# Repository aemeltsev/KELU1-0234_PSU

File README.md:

# KELU1-0234PSU

![PCB image][KELU1-0234-PCB]

[KELU1-0234-PCB]: https://github.com/aemeltsev/KELU1-0234_PSU/blob/master/hw/KELU1-0234PSU_0.1rev.A/KELU1-0234-PCB.png

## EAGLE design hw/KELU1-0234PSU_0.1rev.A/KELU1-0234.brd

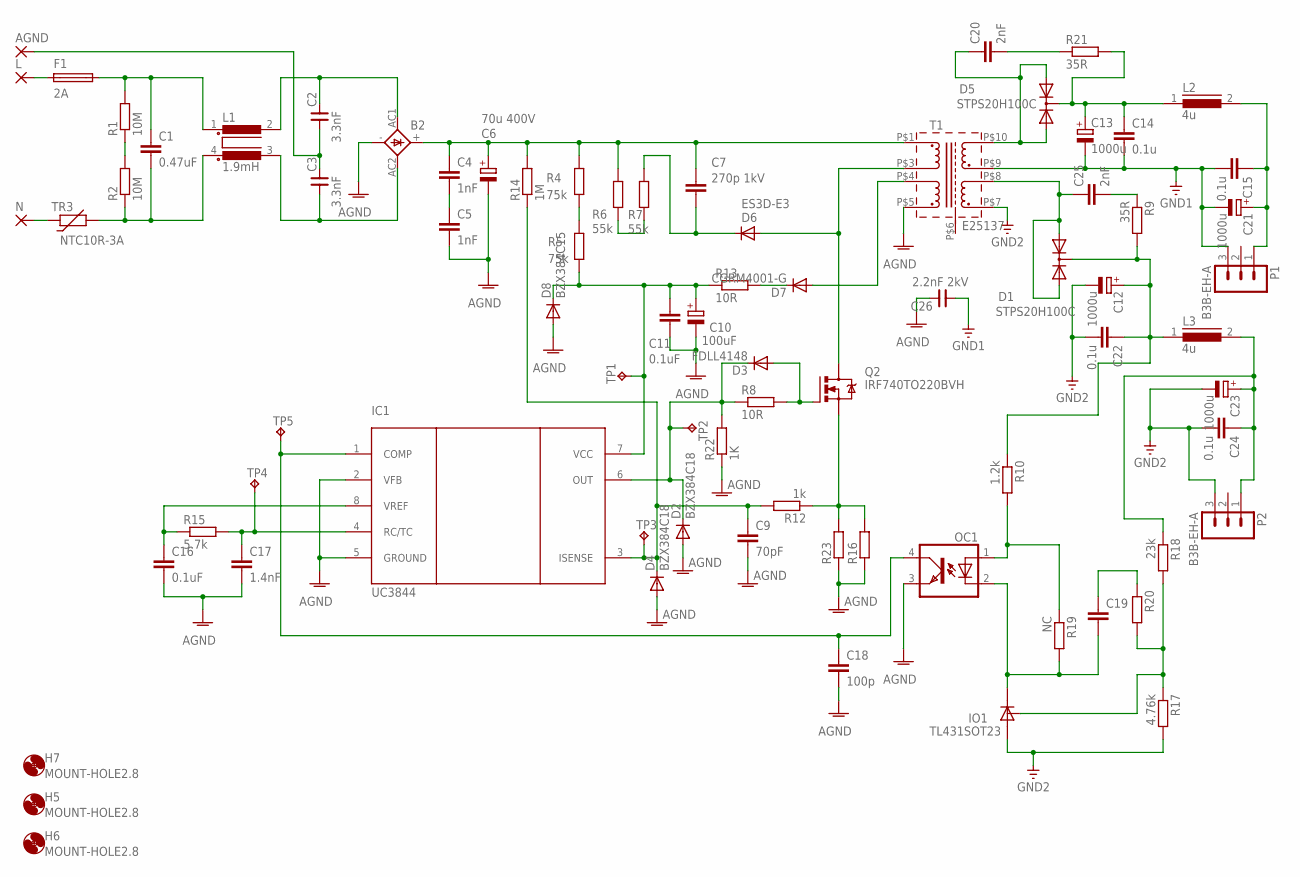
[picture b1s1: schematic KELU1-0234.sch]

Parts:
AGND: 3,17/1,1
B2: 2KBP
C1: 0.47uF; C15B5
C2: 3.3nF; C085-110X050
C3: 3.3nF; C080-110X045
C4, C5: 1nF; C1206K
C6: 70u 400V; E7,5-16
C7: 270p 1kV; C1206K
C9: 70pF; C0805K
C10: 100uF; E5-5
C11, C16: 0.1uF; C0805K
C12, C13, C21, C23: 1000u; E3,5-8
C14, C15, C22, C24: 0.1u; C0805K
C17: 1.4nF; C0805K
C18: 100p; C0805K
C19: C-EUC0805K; C0805K
C20, C25: 2nF; C1206K
C26: 2.2nF 2kV; C080-110X045
D1, D5: STPS20H100C; TO220ABS
D2, D4: BZX384C18; SOD323-W
D3: FDLL4148; MINIMELF
D6: ES3D-E3; SMC
D7: CGRM4001-G; SOD-123_MINI-SMA
D8: BZX384C15; SOD323-W
F1: 2A; TE5
H5, H6, H7: MOUNT-HOLE2.8; 2,8
IC1: UC3844; SOIC08
IO1: TL431SOT23; SOT23
L: 3,17/1,1
L1: 1.9mH; MFE
L2, L3: 4u; 82114R
N: 3,17/1,1
OC1: PC817; DIL04
P1, P2: B3B-EH-A
Q2: IRF740TO220BVH; TO220BVH
R1, R2: 10M; M1206
R4, R5: 75k; M1206
R6, R7: 55k; M1206
R8: 10R; M1206
R9, R21: 35R; M1206
R10: 1.2k; R0805W
R12: 1k; R0805W
R13: 10R; R0805W
R14: 1M; M1206
R15: 5.7k; R0805W
R16, R23: R-EU_R2512; R2512
R17: 4.76k; R0805W
R18: 23k; R0805W
R19: NC; R0805W
R20: R-EU_R0805W; R0805W
R22: 1K; M1206
T1: E25137
TP1, TP2, TP3, TP4, TP5: TPB1,27; B1,27
TR3: NTC10R-3A; R-5

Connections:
AGND: B2.-, C5.2, C6.-, C9.2, C10.-, C11.2, C16.2, C17.2, C18.2, C26.2, D2.A, D4.A, D8.A, IC1.2 (VFB), IC1.5 (GROUND), OC1.3 (EMIT), R16.1, R22.1, R23.1, T1.P$5 (5)
GND1: C13.-, C14.2, C15.2, C21.-, C26.1, P1.3, T1.P$9 (9)
GND2: C12.-, C22.2, C23.-, C24.2, IO1.3 (A), P2.3, R17.2, T1.P$7 (7)
unnamed: F1.1, L.1
unnamed: C1.1, F1.2, L1.1, R1.2
unnamed: C1.2, L1.4 (3), R2.1, TR3.2
unnamed: R1.1, R2.2
unnamed: AGND.1, C2.1, C3.2
unnamed: N.1, TR3.1
unnamed: B2.AC1, C2.2, L1.2
unnamed: B2.AC2, C3.1, L1.3 (4)
unnamed: B2.+, C4.1, C6.+, C7.1, R4.2, R6.2, R14.2, T1.P$1 (1)
unnamed: C4.2, C5.1
unnamed: D6.A, Q2.D, T1.P$3 (3)
unnamed: D3.A, Q2.G, R8.2
unnamed: R4.1, R5.2
unnamed: D2.C, D3.C, IC1.6 (OUT), R8.1, R22.2, TP2.PP
unnamed: R6.1, R7.1
unnamed: C10.+, C11.1, D8.C, IC1.7 (VCC), R5.1, R13.1, TP1.PP
unnamed: C7.2, D6.C, R7.2
unnamed: C12.+, C22.1, D1.C, L3.1, R9.2, R10.1
unnamed: Q2.S, R12.1, R16.2, R23.2
unnamed: D7.C, R13.2
unnamed: D7.A, T1.P$4 (4)
unnamed: C9.1, D4.C, IC1.3 (ISENSE), R12.2, R14.1, TP3.PP
unnamed: OC1.1 (A), R10.2, R19.1
unnamed: C16.1, IC1.8 (VREF), R15.1
unnamed: C17.1, IC1.4 (RC/TC), R15.2, TP4.PP
unnamed: C20.1, D5.A1, D5.A2, T1.P$10 (10)
unnamed: C13.+, C14.1, D5.C, L2.1, R21.2
unnamed: C15.1, C21.+, L2.2, P1.1
unnamed: C18.1, IC1.1 (COMP), OC1.4 (COL), TP5.PP
unnamed: IO1.2 (R), R17.1, R18.2, R20.2
unnamed: C19.1, R20.1
unnamed: C20.2, R21.1
unnamed: C19.2, IO1.1 (C), OC1.2 (C), R19.2
unnamed: C25.1, D1.A1, D1.A2, T1.P$8 (8)
unnamed: C25.2, R9.1
unnamed: C23.+, C24.1, L3.2, P2.1, R18.1

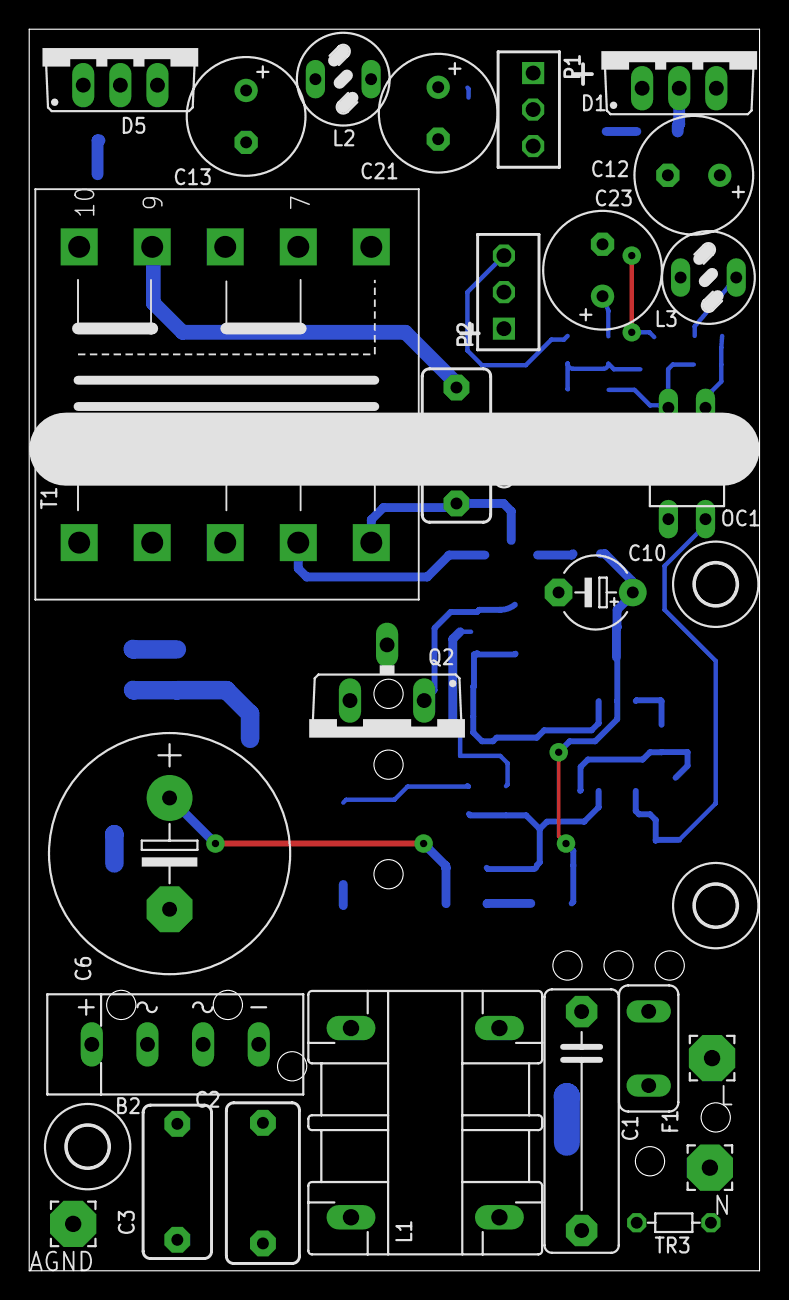
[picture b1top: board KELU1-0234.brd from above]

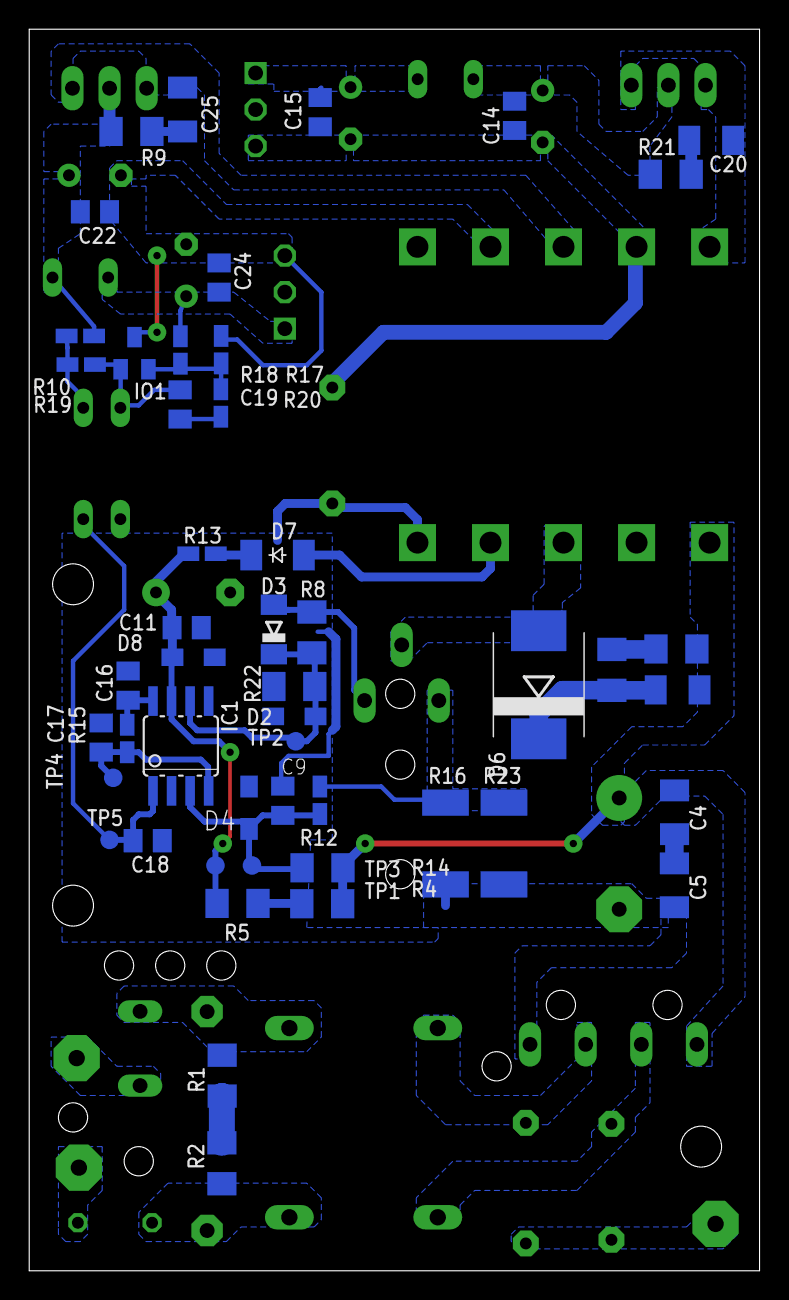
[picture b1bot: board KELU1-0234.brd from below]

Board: 2 copper layers, 50.0 x 85.0 mm, 78 parts (49 on the bottom side), 39 nets.

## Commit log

2019-01-11 Add project file
    Add project file
2019-01-11 Editing
    Editing pcb add pcb image
2019-01-11 Update README.md
    Add pcb image
2019-01-11 Update README.md
    Add image file
2019-01-17 Update
    update revision
2019-01-17 Update README.md
    Edit readme
2019-01-17 Update
    Update pcb image
2019-01-17 Revert "Update"
    This reverts commit e262ecb1de31ac634c25b05378be0f730255bc1c.
2019-01-17 Add image
    Add new image pcb
2019-01-17 Update
    Update circuit
2019-07-15 Edit
    Edit
2020-04-06 add file
    remove LT1244_PSU.asc, add LT1241.pdf, UC3844.pdf tech note and ltspice sim files
2020-04-06 update
    update sim file, add image output

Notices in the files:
parts and their libraries:
con-jst-eh: Copyright (C) 2016, Bob Starr
